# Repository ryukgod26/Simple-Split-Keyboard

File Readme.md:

# Split Keyboard
This is a Simple Split Wireless Keyboard.

## Why
I maded this Kyeboard because making keyboards are Cool and my current Keyboard Sucks. Also Split Keyboards are very col to use and even cooler to make (I can flex on my friends). Also It teaches me many new things like QMk and how to route a complex pcb (by doing it again and again).

## Zine

## Case

## BOM(Bill Of Materials)
|Name|Quantity| Total Cost (USD) | Link | Distributor|
|----|--------|------------------|------|------------|
| PCB | 1 | $46(₹4341) | [Link](https://www.lioncircuits.com/quote) | Lion Circuits |
| Keycaps | 1 | $22 | [Link](https://curiositycaps.in/products/horizon-v2-low-profile-uniform-profile-double-shot-keycap-set-118-key?_pos=3&_sid=d336dd48b&_ss=r) | Curosity Caps |
| Switches | 10 |$5 | [Link](https://neomacro.in/products/kailh-choc-v1-switches?srsltid=AfmBOop8VEBvw5jO73KmpeoEoCvW3SgRwyl2SDaHEtLuj7axHcK_P6oF) | neomarco |
| SuperMini nRF52840 | 2 | [Link](https://robokits.co.in/iot-wireless-solutions/iot-internet-of-things/iot-esp-module/supermini-nrf52840-pro-micro-bluetooth-le-ble-controller-arduino-compatible?srsltid=AfmBOooEiBmOdqCzCmp3A8RQ1pqttlEx7MZDfj-9yJhzAsLnhXO5BfSl) | Robokits |

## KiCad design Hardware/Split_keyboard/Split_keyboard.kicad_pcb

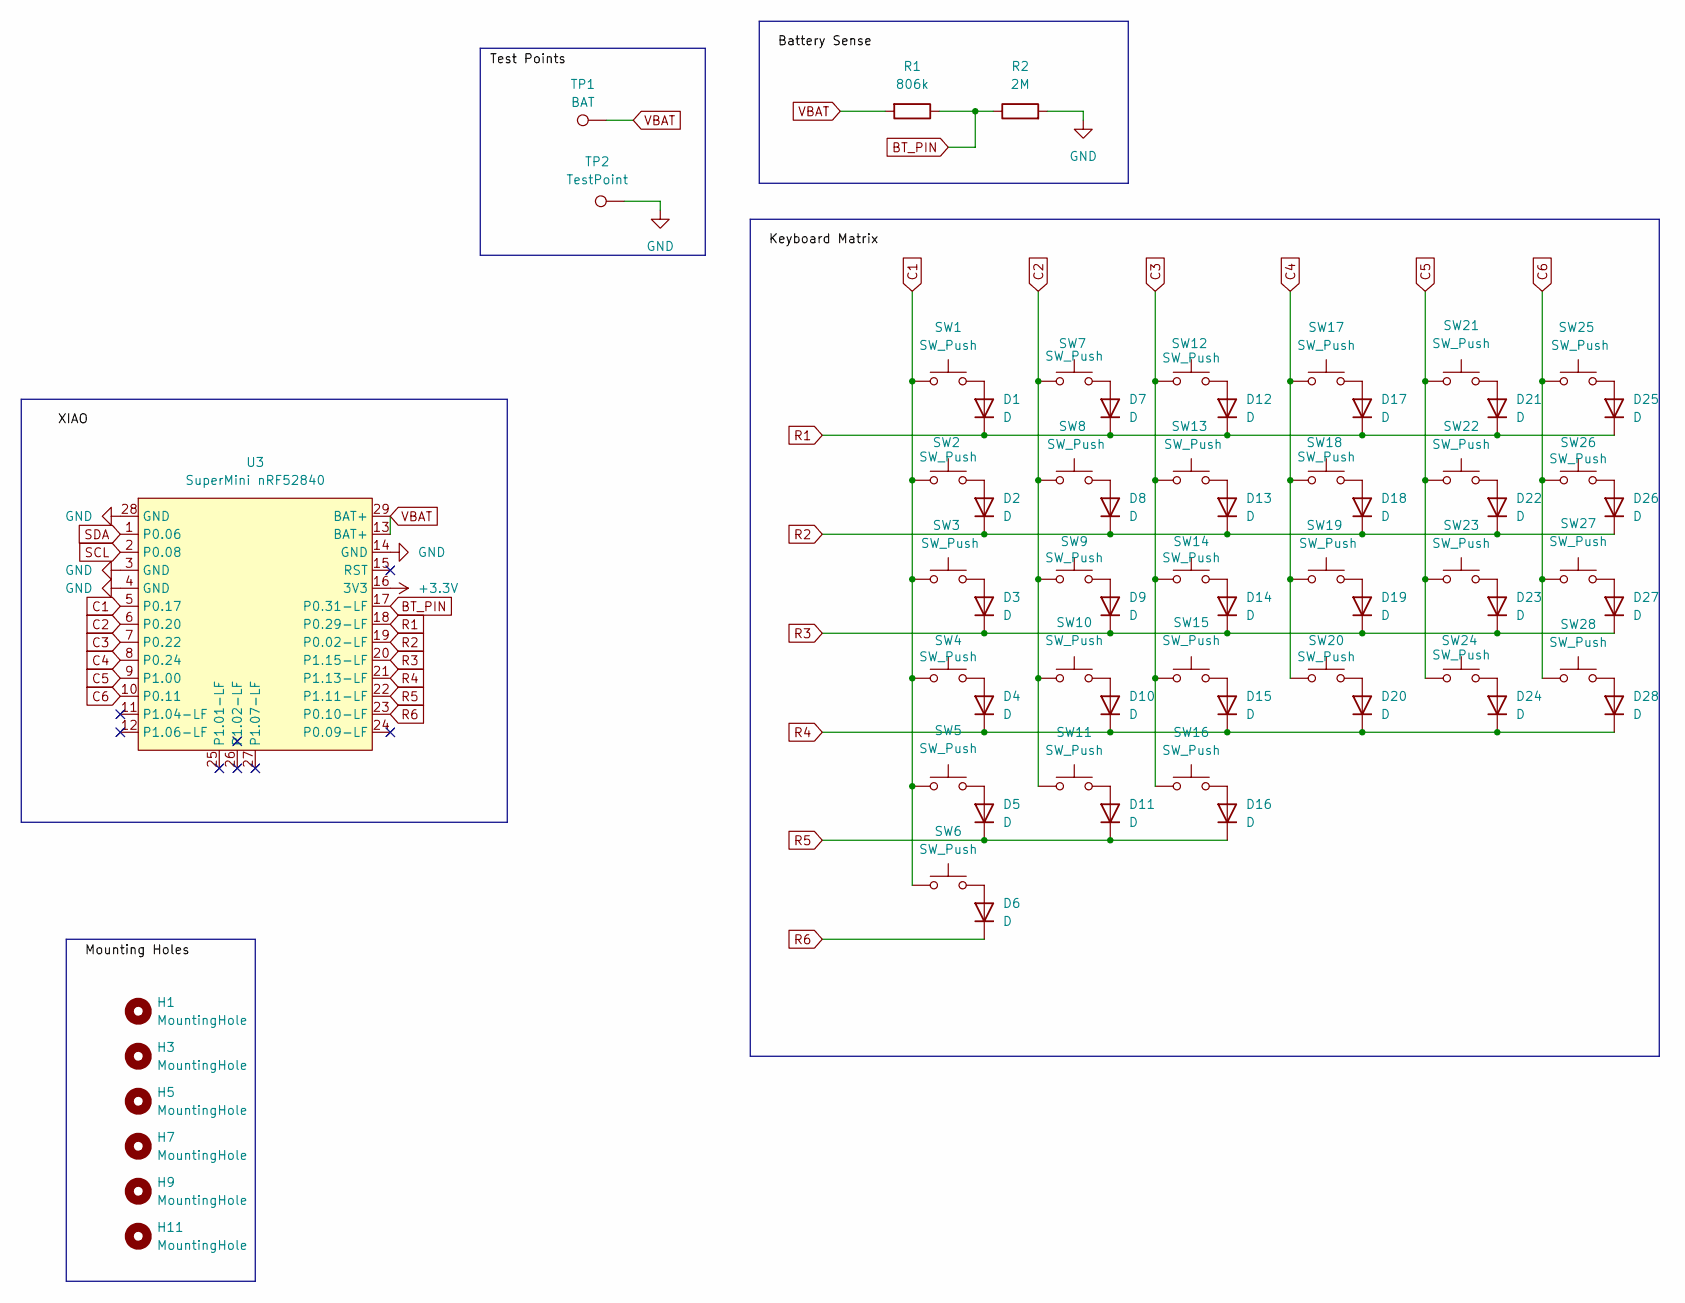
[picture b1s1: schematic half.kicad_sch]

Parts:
D1, D2, D3, D4, D5, D6, D7, D8, D9, D10, D11, D12, D13, D14, D15, D16, D17, D18, D19, D20, D21, D22, D23, D24, D25, D26, D27, D28: D; D_SOD-123
H1, H3, H5, H7, H9, H11: MountingHole; MountingHole_2.2mm_M2
R1: 806k; R_0805_2012Metric
R2: 2M; R_0805_2012Metric
SW1, SW2, SW3, SW4, SW5, SW6, SW7, SW8, SW9, SW10, SW11, SW12, SW13, SW14, SW15, SW16, SW17, SW18, SW19, SW20, SW21, SW22, SW23, SW24, SW25, SW26, SW27, SW28: SW_Push; SW_choc_v1_HS_CPG135001S30_1u
TP1: BAT; TestPoint_Pad_D2.0mm
TP2: TestPoint; TestPoint_Pad_D2.0mm
U3: SuperMini nRF52840; SuperMini_nRF52840_AH_USBup

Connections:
+3.3V: U3.16 (3V3); also elsewhere on the board
BT_PIN: R1.1, R2.1, U3.17 (P0.31-LF); also elsewhere on the board
C1: SW1.1, SW2.1, SW3.1, SW4.1, SW5.1, SW6.1, U3.5 (P0.17); also elsewhere on the board
C2: SW7.1, SW8.1, SW9.1, SW10.1, SW11.1, U3.6 (P0.20); also elsewhere on the board
C3: SW12.1, SW13.1, SW14.1, SW15.1, SW16.1, U3.7 (P0.22); also elsewhere on the board
C4: SW17.1, SW18.1, SW19.1, SW20.1, U3.8 (P0.24); also elsewhere on the board
C5: SW21.1, SW22.1, SW23.1, SW24.1, U3.9 (P1.00); also elsewhere on the board
C6: SW25.1, SW26.1, SW27.1, SW28.1, U3.10 (P0.11); also elsewhere on the board
GND: R2.2, TP2.1, U3.3 (GND), U3.4 (GND), U3.14 (GND), U3.28 (GND); also elsewhere on the board
unnamed: D1.2 (A), SW1.2
unnamed: D2.2 (A), SW2.2
unnamed: D3.2 (A), SW3.2
unnamed: D4.2 (A), SW4.2
unnamed: D5.2 (A), SW5.2
unnamed: D6.2 (A), SW6.2
unnamed: D7.2 (A), SW7.2
unnamed: D8.2 (A), SW8.2
unnamed: D9.2 (A), SW9.2
unnamed: D10.2 (A), SW10.2
unnamed: D11.2 (A), SW11.2
unnamed: D12.2 (A), SW12.2
unnamed: D13.2 (A), SW13.2
unnamed: D14.2 (A), SW14.2
unnamed: D15.2 (A), SW15.2
unnamed: D16.2 (A), SW16.2
unnamed: D17.2 (A), SW17.2
unnamed: D18.2 (A), SW18.2
unnamed: D19.2 (A), SW19.2
unnamed: D20.2 (A), SW20.2
unnamed: D21.2 (A), SW21.2
unnamed: D22.2 (A), SW22.2
unnamed: D23.2 (A), SW23.2
unnamed: D24.2 (A), SW24.2
unnamed: D25.2 (A), SW25.2
unnamed: D26.2 (A), SW26.2
unnamed: D27.2 (A), SW27.2
unnamed: D28.2 (A), SW28.2
R1: D1.1 (K), D7.1 (K), D12.1 (K), D17.1 (K), D21.1 (K), D25.1 (K), U3.18 (P0.29-LF); also elsewhere on the board
R2: D2.1 (K), D8.1 (K), D13.1 (K), D18.1 (K), D22.1 (K), D26.1 (K), U3.19 (P0.02-LF); also elsewhere on the board
R3: D3.1 (K), D9.1 (K), D14.1 (K), D19.1 (K), D23.1 (K), D27.1 (K), U3.20 (P1.15-LF); also elsewhere on the board
R4: D4.1 (K), D10.1 (K), D15.1 (K), D20.1 (K), D24.1 (K), D28.1 (K), U3.21 (P1.13-LF); also elsewhere on the board
R5: D5.1 (K), D11.1 (K), D16.1 (K), U3.22 (P1.11-LF); also elsewhere on the board
R6: D6.1 (K), U3.23 (P0.10-LF); also elsewhere on the board
SCL: U3.2 (P0.08); also elsewhere on the board
SDA: U3.1 (P0.06); also elsewhere on the board
VBAT: R1.2, TP1.1, U3.13 (BAT+), U3.29 (BAT+); also elsewhere on the board

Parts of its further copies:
D29, D30, D31, D32, D33, D34, D35, D36, D37, D38, D39, D40, D41, D42, D43, D44, D45, D46, D47, D48, D49, D50, D51, D52, D53, D54, D55, D56: D; D_SOD-123
H2, H4, H6, H8, H10, H12: MountingHole; MountingHole_2.2mm_M2
R3: 806k; R_0805_2012Metric
R4: 2M; R_0805_2012Metric
SW29, SW30, SW31, SW32, SW33, SW34, SW35, SW36, SW37, SW38, SW39, SW40, SW41, SW42, SW43, SW44, SW45, SW46, SW47, SW48, SW49, SW50, SW51, SW52, SW53, SW54, SW55, SW56: SW_Push; SW_choc_v1_HS_CPG135001S30_1u
TP3: BAT; TestPoint_Pad_D2.0mm
TP4: TestPoint; TestPoint_Pad_D2.0mm
U4: SuperMini nRF52840; SuperMini_nRF52840_AH_USBup

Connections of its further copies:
+3.3V: U4.16 (3V3); also elsewhere on the board
BT_PIN: R3.1, R4.1, U4.17 (P0.31-LF); also elsewhere on the board
C1: SW29.1, SW30.1, SW31.1, SW32.1, SW33.1, SW34.1, U4.5 (P0.17); also elsewhere on the board
C2: SW35.1, SW36.1, SW37.1, SW38.1, SW39.1, U4.6 (P0.20); also elsewhere on the board
C3: SW40.1, SW41.1, SW42.1, SW43.1, SW44.1, U4.7 (P0.22); also elsewhere on the board
C4: SW45.1, SW46.1, SW47.1, SW48.1, U4.8 (P0.24); also elsewhere on the board
C5: SW49.1, SW50.1, SW51.1, SW52.1, U4.9 (P1.00); also elsewhere on the board
C6: SW53.1, SW54.1, SW55.1, SW56.1, U4.10 (P0.11); also elsewhere on the board
GND: R4.2, TP4.1, U4.3 (GND), U4.4 (GND), U4.14 (GND), U4.28 (GND); also elsewhere on the board
unnamed: D29.2 (A), SW29.2
unnamed: D30.2 (A), SW30.2
unnamed: D31.2 (A), SW31.2
unnamed: D32.2 (A), SW32.2
unnamed: D33.2 (A), SW33.2
unnamed: D34.2 (A), SW34.2
unnamed: D35.2 (A), SW35.2
unnamed: D36.2 (A), SW36.2
unnamed: D37.2 (A), SW37.2
unnamed: D38.2 (A), SW38.2
unnamed: D39.2 (A), SW39.2
unnamed: D40.2 (A), SW40.2
unnamed: D41.2 (A), SW41.2
unnamed: D42.2 (A), SW42.2
unnamed: D43.2 (A), SW43.2
unnamed: D44.2 (A), SW44.2
unnamed: D45.2 (A), SW45.2
unnamed: D46.2 (A), SW46.2
unnamed: D47.2 (A), SW47.2
unnamed: D48.2 (A), SW48.2
unnamed: D49.2 (A), SW49.2
unnamed: D50.2 (A), SW50.2
unnamed: D51.2 (A), SW51.2
unnamed: D52.2 (A), SW52.2
unnamed: D53.2 (A), SW53.2
unnamed: D54.2 (A), SW54.2
unnamed: D55.2 (A), SW55.2
unnamed: D56.2 (A), SW56.2
R1: D29.1 (K), D35.1 (K), D40.1 (K), D45.1 (K), D49.1 (K), D53.1 (K), U4.18 (P0.29-LF); also elsewhere on the board
R2: D30.1 (K), D36.1 (K), D41.1 (K), D46.1 (K), D50.1 (K), D54.1 (K), U4.19 (P0.02-LF); also elsewhere on the board
R3: D31.1 (K), D37.1 (K), D42.1 (K), D47.1 (K), D51.1 (K), D55.1 (K), U4.20 (P1.15-LF); also elsewhere on the board
R4: D32.1 (K), D38.1 (K), D43.1 (K), D48.1 (K), D52.1 (K), D56.1 (K), U4.21 (P1.13-LF); also elsewhere on the board
R5: D33.1 (K), D39.1 (K), D44.1 (K), U4.22 (P1.11-LF); also elsewhere on the board
R6: D34.1 (K), U4.23 (P0.10-LF); also elsewhere on the board
SCL: U4.2 (P0.08); also elsewhere on the board
SDA: U4.1 (P0.06); also elsewhere on the board
VBAT: R3.2, TP3.1, U4.13 (BAT+), U4.29 (BAT+); also elsewhere on the board

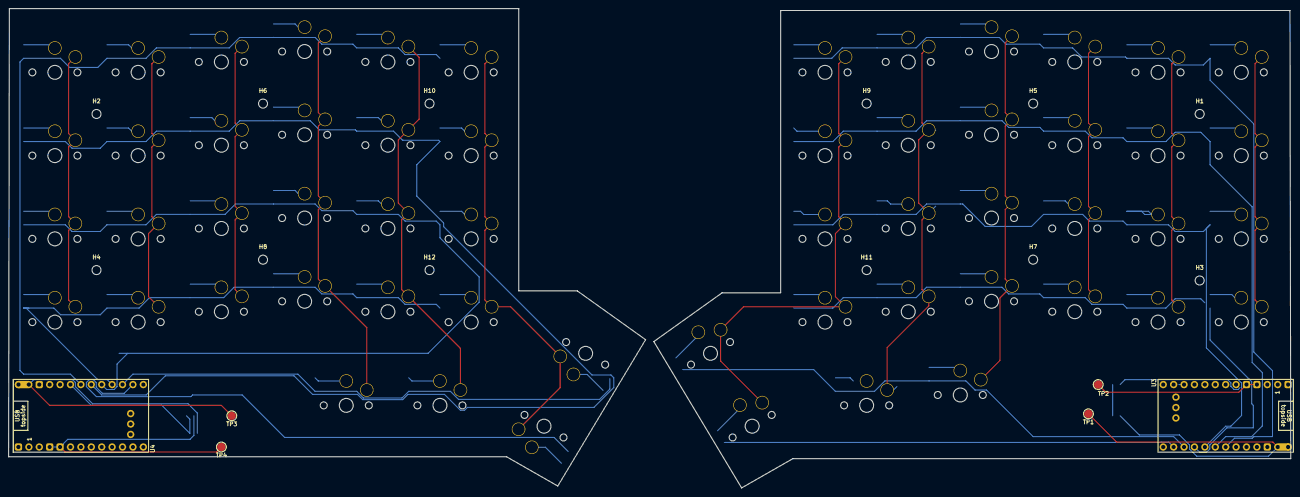
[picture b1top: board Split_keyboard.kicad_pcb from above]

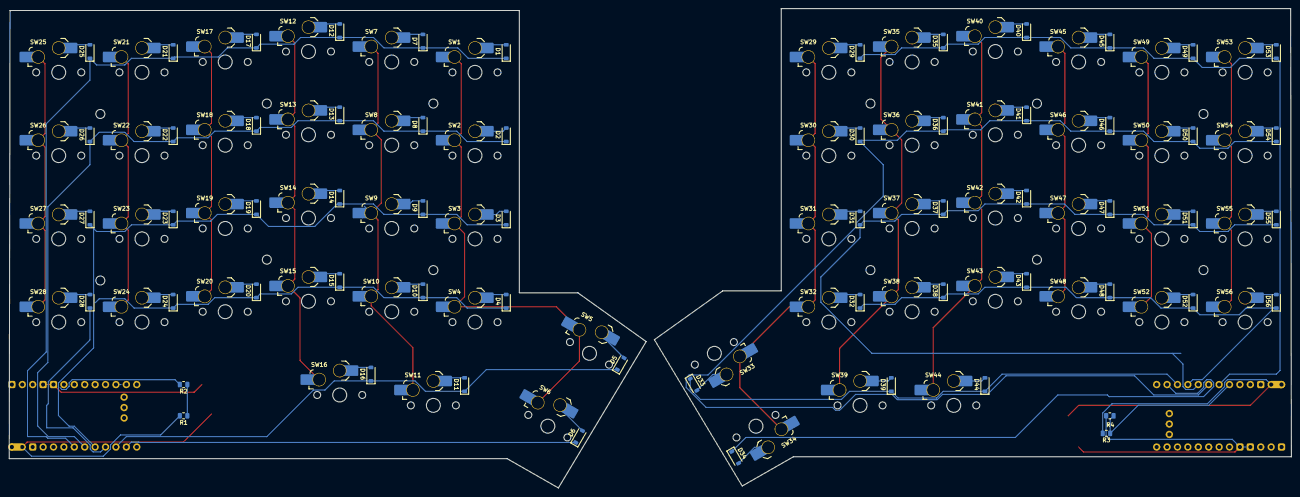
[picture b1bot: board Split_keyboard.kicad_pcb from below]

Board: 2 copper layers, 312.9 x 117.0 mm, 134 parts (116 on the bottom side), 74 nets.

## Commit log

2026-05-29 Added Schematics for the Switches and the main chip of the keyboard in kicad
2026-05-31 Added 3D models and pcb
2026-06-05 Assigned footprints and imported them into the footprint editor
2026-06-05 Changed the design of the footprints and maded it simliar to keeb.io keyboards
2026-06-06 Added right side and added edge.cuts for the pcb on both sides
2026-06-12 Changed the design of the keyboard completelty with schematis
2026-06-19 Add initial schematic and PDF documentation for split keyboard design
    - Created a new schematic file for the split keyboard in KiCad format.
    - Added a PDF document for the split keyboard design.
2026-06-21 Add initial files for Split Wireless Keyboard project
    - Created Gerber job file for PCB layout.
    - Added ZIP archive containing Gerber files.
    - Introduced README.md with project overview, case images, and BOM.
    - Included zine images in various formats (JPEG, PNG, PDF) for project documentation.
2026-06-21 Remove lock files for Split Keyboard and add new images for QR code and zine
